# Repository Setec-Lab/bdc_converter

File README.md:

BDC Prototype -- README {#mainpage}
============

### Most recent version of this repository can be found in: ###

* [Bitbucket](https://bitbucket.org/juanjorojash/bdc_prototype/src/master)

### Documentation ###

* Full documentation in HTLM version can be found in **documentation/htlm/index.htlm**

### What is this repository for? ###

* This repository was created to be used in conjuction with the integrated system known as "BDC_Prototype.V1.1". It was created to control the PIC16F1786 installed for feedback control, and serial logging.
* Hardware version: BDC_Prototype.V1.1

### How do I get set up? ###

* Connect usign serial cable. 
* **Serial terminal** Start with the following settings BR:19200 kbps, Data: 8 bit, Parity: none, Stop bits: 1, Flow control: none. 
* **LabView logger program** A program for receiving, saving and plotting the test data is included in the repository, in the directory **logger/main.vi**. The following programs are needed in order to run this program in a PC that **does not** have LabView installed:
	* [LabVIEW Run-Time Engine 2016 - (64-bit)](http://www.ni.com/download/labview-run-time-engine-2016/6067/en/) 
	* [NI-VISA Run-Time Engine 16.0](http://www.ni.com/download/ni-visa-run-time-engine-16.0/6188/en/)
The program creates the directory **c:/BDC_logger_data** to store the data.

### Contribution guidelines ###

* If you want to propose a review or need to modify the code for any reason first clone this [repository](https://bitbucket.org/juanjorojash/bdc_prototype/src/master) in your PC and create a new branch for your changes. Once your changes are complete and fully tested ask the administrator permission to push this new branch into the source.
* If you just want to do local changes instead you can download a zip version of the repository and do all changes locally in your PC. 

### Who do I talk to? ###

* [Juan J. Rojas](mailto:juan.rojas@itcr.ac.cr)

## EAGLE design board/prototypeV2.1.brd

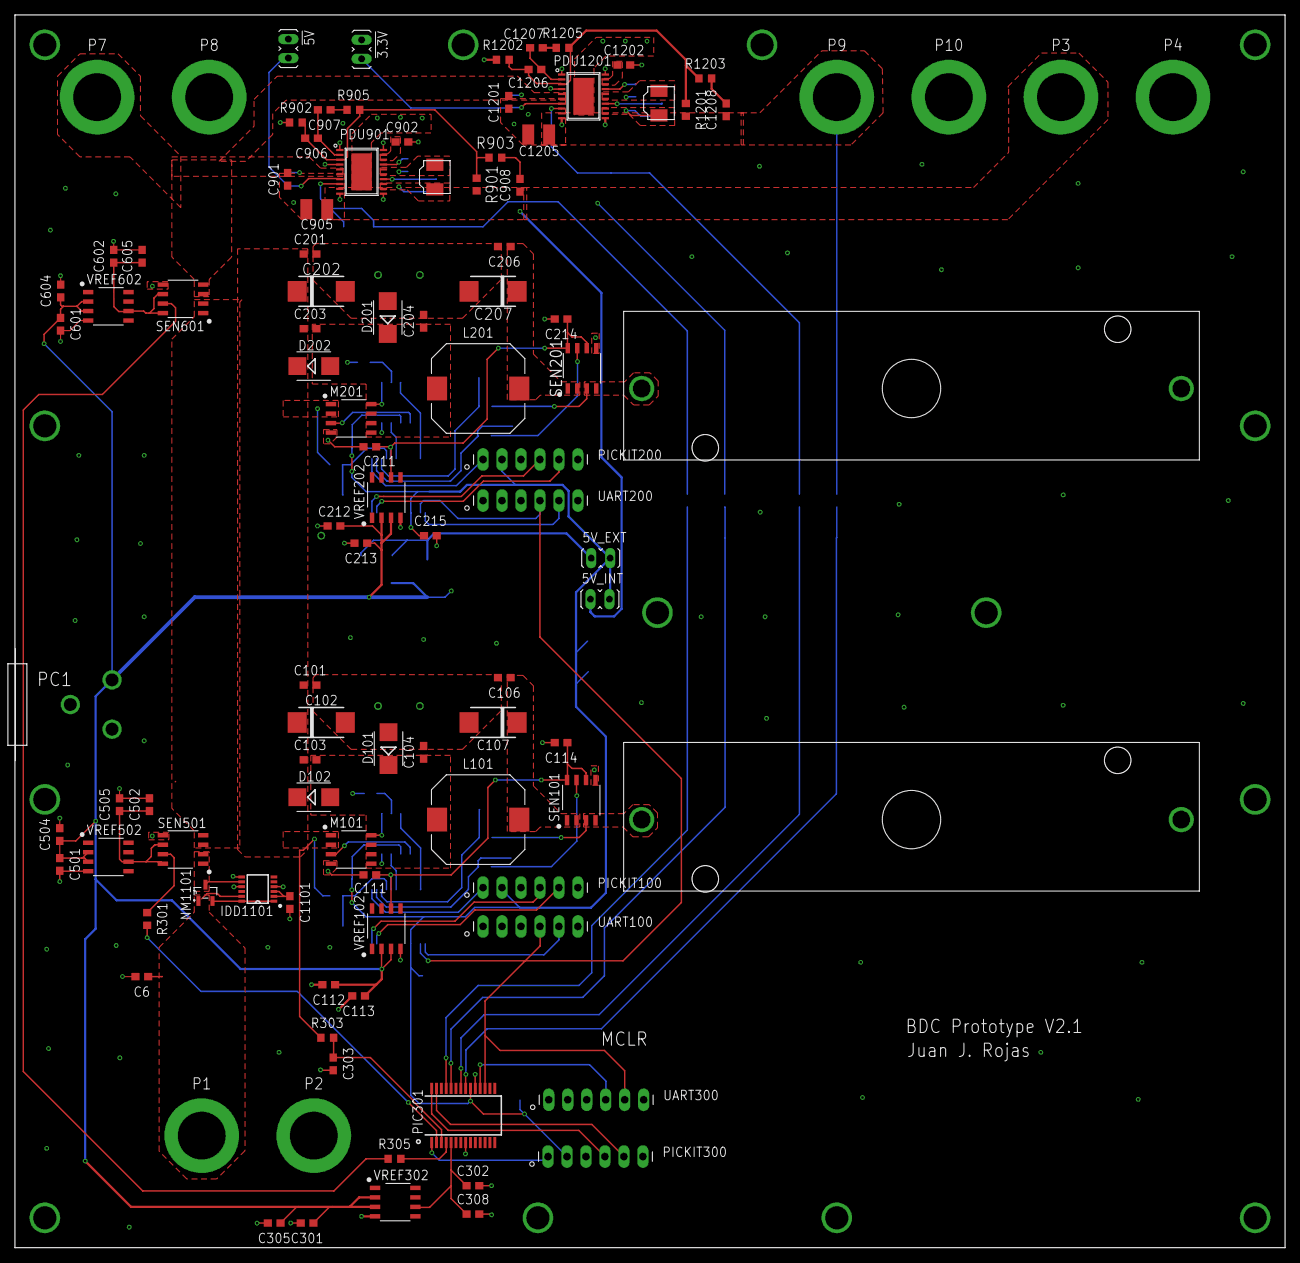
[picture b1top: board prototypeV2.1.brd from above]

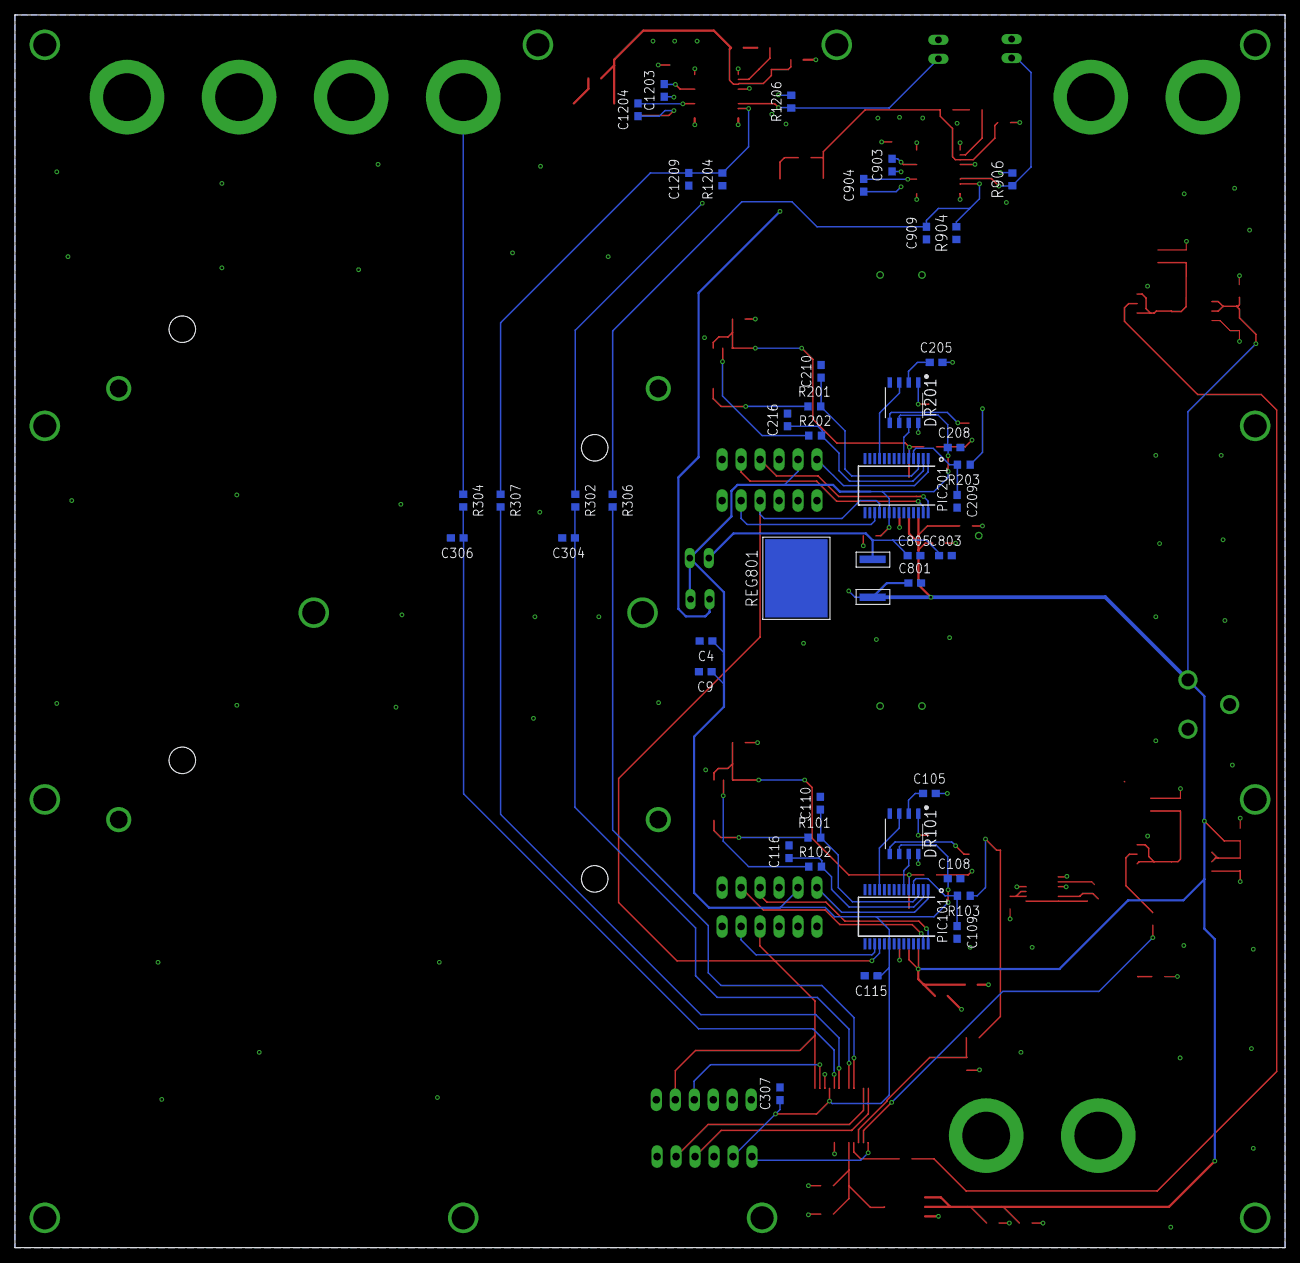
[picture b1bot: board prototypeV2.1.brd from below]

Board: 2 copper layers, 170.0 x 165.0 mm, 148 parts (44 on the bottom side), 85 nets.

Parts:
5V_EXT, 5V_INT: J2P
!3.3V, !5V: J2P
C4, C109, C110, C114, C115, C209, C210, C214, C215, C303, C304, C306, C307, C308, C505, C605, C903, C904, C1101, C1203, C1204: 0.1u; C0603
C6, C101, C105, C106, C111, C113, C201, C205, C206, C211, C213, C302, C305, C502, C504, C602, C604, C803, C902, C1202: 1u; C0603
C9, C112, C212, C301, C501, C601, C805, C901: 10u; C0603
C102, C107, C202, C207: 33u; C7343
C103, C104, C116, C203, C204, C216: 1n; C0603
C108, C208: 2.2u; C0603
C801: 0.33u; C0603
C905, C1205: 47u; C1210
C906: 22p; C0603
C907: 680p; C0603
C908: 47p; C0603
C909, C1209: 100p; C0603
C1201: 22u; C0603
C1206: 15p; C0603
C1207: 820p; C0603
C1208: 56p; C0603
CELL1, CELL2: CELL18650_HOLDER; 18650_HOLDER
D101, D102, D201, D202: SMB
DR101, DR201: TPS28225D; SOIC-8
IDD1101: LTC4352CMS; MSOP12
L101, L201: 22u; CLF12555
L901, L1201: 4.7u; SPM4020T
M101, M201: SI4914BDY; SOIC-8
NM1101: IRLML6244TRPBF; SOT-23
P1, P2, P3, P4, P7, P8, P9, P10: TJ-563
PC1: 722RA
PDU901, PDU1201: LTC3112EFE; TSSOP20CA
PIC101, PIC201, PIC301: PIC16F1786-I/SS; SSOP28
PICKIT100, PICKIT200, PICKIT300: MA06-1
R101, R103, R201, R203, R302, R303, R304: 200; R0603
R102, R202, R301, R305, R306, R307: 0; R0603
R901: 845k; R0603
R902: 158k; R0603
R903, R906, R1206: 10k; R0603
R904, R1204: 42.2k; R0603
R905: 33k; R0603
R1201: 620k; R0603
R1202: 200k; R0603
R1203: 9.1k; R0603
R1205: 39k; R0603
REG801: NCV7805BD2TG; D2PAK-3
SEN101, SEN201, SEN501, SEN601: ACS723-05AB-T; SOIC-8
UART100, UART200, UART300: MA06-1
VREF102, VREF202, VREF302, VREF502, VREF602: REF195GSZ; SOIC-8

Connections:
3.3V_PL: C1205.1, C1208.1, P9.P, PDU1201.9, R304.1, R1201.2
5V_ON: !5V.2, PDU901.7, R906.1
5V_PL: 5V_INT.1, C905.1, C908.1, P3.P, PDU901.9, R302.1, R901.2
7.5V: C112.1, C113.1, C212.1, C213.1, C301.1, C305.1, C501.1, C504.1, C601.1, C604.1, C801.1, PC1.PIN, REG801.1, VREF102.2, VREF102.3, VREF202.2, VREF202.3, VREF302.2, VREF302.3, VREF502.2, VREF502.3, VREF602.2, VREF602.3
12V_ON: !3.3V.2, PDU1201.7, R1206.1
+5V: 5V_EXT.2, 5V_INT.2, C4.1, C9.1, C108.1, C115.1, C208.1, C215.1, C307.1, DR101.6, DR201.6, PIC101.20, PIC201.20, PIC301.20, PICKIT100.2, PICKIT200.2, PICKIT300.2
COM_RX: PIC101.18, PIC201.18, PIC301.17, UART100.4, UART200.4, UART300.5
CONTROL:5V_REF: C302.1, C308.1, PIC301.5, VREF302.6
CONTROL:ICSPCLK: PIC301.27, PICKIT300.5
CONTROL:ICSPDAT: PIC301.28, PICKIT300.4
CONTROL:I_LOAD: PIC301.4, R305.2
CONTROL:I_PDU_3.3V: PIC301.22, R307.2
CONTROL:I_PDU_5V: PIC301.25, R306.2
CONTROL:I_PV: PIC301.2, R301.2
CONTROL:MCLR: PIC301.1, PICKIT300.1
CONTROL:RX: PIC301.18, UART300.4
CONTROL:V_BUS: C303.1, PIC301.3, R303.2
CONTROL:V_PDU_3.3V: C306.1, PIC301.21, R304.2
CONTROL:V_PDU_5V: C304.1, PIC301.24, R302.2
CONV1:5V_REF: C111.1, C114.1, PIC101.5, SEN101.6, SEN101.8, VREF102.6
CONV1:DR_EN: DR101.7, PIC101.6
CONV1:G1: DR101.1, M101.8
CONV1:G2: DR101.5, M101.3
CONV1:ICSPCLK: PIC101.27, PICKIT100.5
CONV1:ICSPDAT: PIC101.28, PICKIT100.4
CONV1:IS_BAT: C116.1, PIC101.2, R102.2
CONV1:I_BAT: R102.1, SEN101.7
CONV1:LO: C106.1, C107.+, L101.2, SEN101.1, SEN101.2
CONV1:MCLR: PIC101.1, PICKIT100.1
CONV1:N$2: C105.1, DR101.2
CONV1:PWM: DR101.3, PIC101.11
CONV1:SW: C103.2, C104.1, C105.2, D101.C, D102.A, DR101.8, L101.1, M101.5, M101.6, M101.7
CONV1:TX: PIC101.17, UART100.5
CONV1:VS_BAT: C110.1, PIC101.3, R101.2
CONV1:VS_BUS: C109.1, PIC101.4, R103.2
CONV2:5V_REF: C211.1, C214.1, PIC201.5, SEN201.6, SEN201.8, VREF202.6
CONV2:DR_EN: DR201.7, PIC201.6
CONV2:G1: DR201.1, M201.8
CONV2:G2: DR201.5, M201.3
CONV2:ICSPCLK: PIC201.27, PICKIT200.5
CONV2:ICSPDAT: PIC201.28, PICKIT200.4
CONV2:IS_BAT: C216.1, PIC201.2, R202.2
CONV2:I_BAT: R202.1, SEN201.7
CONV2:LO: C206.1, C207.+, L201.2, SEN201.1, SEN201.2
CONV2:MCLR: PIC201.1, PICKIT200.1
CONV2:N$2: C205.1, DR201.2
CONV2:PWM: DR201.3, PIC201.11
CONV2:SW: C203.2, C204.1, C205.2, D201.C, D202.A, DR201.8, L201.1, M201.5, M201.6, M201.7
CONV2:TX: PIC201.17, UART200.5
CONV2:VS_BAT: C210.1, PIC201.3, R201.2
CONV2:VS_BUS: C209.1, PIC201.4, R203.2
GND: !3.3V.1, !5V.1, C4.2, C6.2, C9.2, C101.2, C102.-, C104.2, C106.2, C107.-, C108.2, C109.2, C110.2, C111.2, C112.2, C113.2, C114.2, C115.2, C116.2, C201.2, C202.-, C204.2, C206.2, C207.-, C208.2, C209.2, C210.2, C211.2, C212.2, C213.2, C214.2, C215.2, C216.2, C301.2, C302.2, C303.2, C304.2, C305.2, C306.2, C307.2, C308.2, C501.2, C502.2, C504.2, C505.2, C601.2, C602.2, C604.2, C605.2, C801.2, C803.2, C805.2, C901.2, C902.2, C905.2, C909.1, C1101.2, C1201.2, C1202.2, C1205.2, C1209.1, CELL1.BB1.N, CELL2.BB1.N, D101.A, D201.A, DR101.4, DR201.4, IDD1101.4, IDD1101.7, IDD1101.9, M101.4, M201.4, P2.P, P4.P, P8.P, P10.P, PC1.SLEEVE, PC1.SLEEVE_SHUNT, PDU901.1, PDU901.4, PDU901.10, PDU901.11, PDU901.20, PDU901.21, PDU1201.1, PDU1201.4, PDU1201.10, PDU1201.11, PDU1201.20, PDU1201.21, PIC101.8, PIC101.19, PIC201.8, PIC201.19, PIC301.8, PIC301.19, PICKIT100.3, PICKIT200.3, PICKIT300.3, R902.1, R904.1, R1202.1, R1204.1, REG801.4, SEN101.5, SEN201.5, SEN501.5, SEN601.5, UART100.1, UART200.1, UART300.1, VREF102.4, VREF202.4, VREF302.4, VREF502.4, VREF602.4
IDEAL_D1:N$1: IDD1101.1, IDD1101.12, NM1101.2
IDEAL_D1:N$4: C1101.1, IDD1101.2, IDD1101.3
IS_LOAD: R305.1, SEN601.7
IS_PDU_3.3V: C1209.2, PDU1201.8, R307.1, R1204.2
IS_PDU_5V: C909.2, PDU901.8, R306.1, R904.2
IS_PV: R301.1, SEN501.7
LOAD_BUS: C901.1, C1201.1, P7.P, PDU901.5, PDU901.6, PDU1201.5, PDU1201.6, R906.2, R1206.2, SEN601.3, SEN601.4
unnamed: CELL1.BB1.P, R101.1, SEN101.3, SEN101.4
unnamed: CELL2.BB1.P, R201.1, SEN201.3, SEN201.4
unnamed: 5V_EXT.1, C803.1, C805.1, REG801.3
unnamed: IDD1101.8, NM1101.3, SEN501.1, SEN501.2
PDU_3.3V:N$1: C1203.2, PDU1201.17
PDU_3.3V:N$2: C1202.1, PDU1201.18, PDU1201.19
PDU_3.3V:N$3: C1204.2, PDU1201.14
PDU_3.3V:N$4: C1203.1, L1201.1, PDU1201.15, PDU1201.16
PDU_3.3V:N$5: C1207.1, R1205.1
PDU_3.3V:N$6: C1206.1, C1207.2, PDU1201.2
PDU_3.3V:N$7: C1204.1, L1201.2, PDU1201.12, PDU1201.13
PDU_3.3V:N$8: C1208.2, R1203.2
PDU_3.3V:N$9: C1206.2, PDU1201.3, R1201.1, R1202.2, R1203.1, R1205.2
PDU_5V:N$1: C903.2, PDU901.17
PDU_5V:N$2: C902.1, PDU901.18, PDU901.19
PDU_5V:N$3: C904.2, PDU901.14
PDU_5V:N$4: C903.1, L901.1, PDU901.15, PDU901.16
PDU_5V:N$5: C907.1, R905.1
PDU_5V:N$6: C906.1, C907.2, PDU901.2
PDU_5V:N$7: C904.1, L901.2, PDU901.12, PDU901.13
PDU_5V:N$8: C908.2, R903.2
PDU_5V:N$9: C906.2, PDU901.3, R901.1, R902.2, R903.1, R905.2
PV: C6.1, IDD1101.11, NM1101.1, P1.P
PV_BUS: C101.1, C102.+, C103.1, C201.1, C202.+, C203.1, D102.C, D202.C, M101.1, M101.2, M201.1, M201.2, R103.1, R203.1, R303.1, SEN501.3, SEN501.4, SEN601.1, SEN601.2
SENS_LOAD:5V_REF: C602.1, C605.1, SEN601.6, SEN601.8, VREF602.6
SENS_PV:5V_REF: C502.1, C505.1, SEN501.6, SEN501.8, VREF502.6

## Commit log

2018-10-22 I think it will be good to try and implement the most recent functions in this program
2018-10-22 I made several changes but not of them really deserve a comment. The board was shorted in the ideal diodes, which make sense because they were bad from the beginning. The ADC is dropping a lot of vol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
2018-10-25 This one is controlling the voltage very well
2018-11-10 Some small changes in the labview program
2018-11-10 Phase difference of half the period between the PMSC1 (master) and PMSC3
2018-11-10 Erase unnecessary files and change the frequency to 125Khz, there's nothing better. Need to change the inductors or put some filter
2018-11-14 Some changes in documentation
2019-01-26 Changes in MPLAB project
2019-01-29 Several changes to make them work with the new electronic load and my new PC
2019-01-30 I chage the control to CC in the electronic load because there were some issues with CP control. Now the PIC also measures battery voltage and next I will include it in the control loop
2019-01-31 Added new files for the profiles and include the protection algorithm
2019-01-31 There was a problem with the upper limit in the labview program, I change it.
2019-02-01 new CC profile with new concept for mission, zero net energy in an orbit
2019-04-02 Change in minimu DC. Added protection above 4150 mV. Added logger used in Cholab computer
2019-06-18 Last cholab pc code,from here it starts the new idea of having an interuption
2019-06-18 It fucking worked!! Now i have an ISR that takes care of the control loop
2019-06-30 Eliminating useless stuff
2019-07-11 New gitnore
2019-07-11 First time it compiles
2019-07-11 There is a problem with the PI controller, I think is different and I just copy it from the other program
2019-07-11 Development board reading correctly but not controlling
2019-07-11 WORKING
2019-07-14 calculation of error
2019-07-16 Erase old logger
2019-07-17 Working very good in development board
2019-07-18 New program, tested with INCREASE every 8 ms
2019-07-23 Converter and controller program
2019-07-24 Several function were changed to pointer-based
2019-07-26 Controller is working but not sending setpoints yet
2019-07-26 Not working for converter
2019-07-26 It controls the converter and the functions are the pointer versions
2019-07-26 Trabajando, solo yogurt
2019-07-27 New labview program
2019-07-27 I found the integrator make the system try to compesate in the opposite way it is expected
2019-07-27 Include reset case
2019-07-30 Configuration in MPLAB for cholab PC
2019-07-30 Reset is not needed, everything can be solved with start
2019-08-02 change in vbusav after adding the voltage divider
2019-08-02 Include libraries , the main for the SAS is missing
2019-08-02 Eliminate logger from converter branch
2019-08-02 Eliminate old logger
2019-08-03 Only one converter test
2019-08-03 Now the voltage increase or decrease in 10 units
2019-08-03 trying with 2
2019-08-03 New approach, duty cycle change!!!
2019-08-03 Plus or minus?
2019-08-03 Change the start and stop macro
2019-08-03 Go back to minus and plus
2019-08-09 Protection of the duty cycle so it is never bigger than the MAX or smaller than the MIN
2019-08-21 Changes in RESET and connected toVref+
2019-08-23 Converter more in sync but still there are some problems
